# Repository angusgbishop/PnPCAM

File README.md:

# PnPCAM
 
PnPCAM is an [Open Hardware](https://www.oshwa.org/definition/) project dedicated to bringing high-quality machine vision to the various open source pick-and-place projects.

This project is very much **in development**, clone at your own risk!

The current versions of the board are based off the OnSemi AR0144 image sensor, as it is avaliable through mainline distributers at a reasonable cost for low quantities. 

* Up-to 1200x800 pixel resolution at 30fps (Currently limited by USB Bridge Chip)
* Global shutter
* Standard Webcam USB out
* <s>Onboard LED with exposure-triggered flash</s> (Requirement Dropped)
* LED Expansion Header for third-party use of the flash signal.
* Triggered shutter mode.
* Onboard lens distortion correction.

# Interested?
[View the Wiki here](https://github.com/angusgbishop/PnPCAM/wiki)

Find me on the [OpenPnP Discord](https://discord.gg/EmsrFVx)

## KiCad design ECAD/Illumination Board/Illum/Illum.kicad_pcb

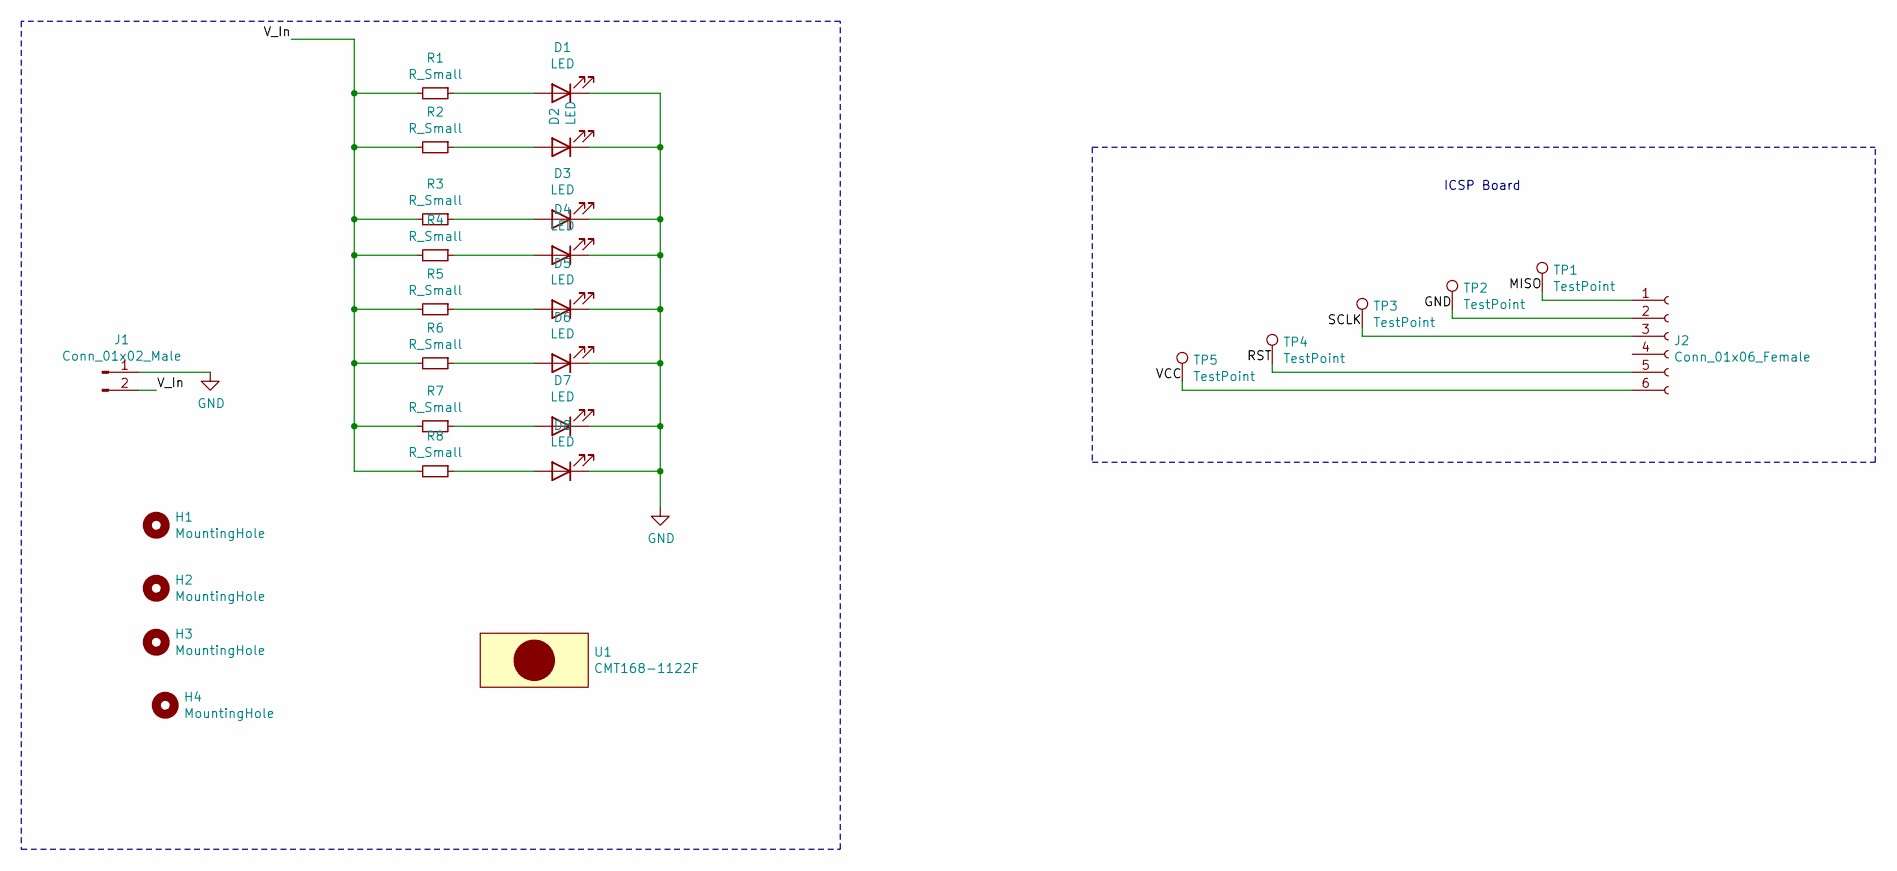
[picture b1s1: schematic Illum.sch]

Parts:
D1, D2, D3, D4, D5, D6, D7, D8: LED; LED_0805_2012Metric
H1, H2, H3, H4: MountingHole; MountingHole_2.2mm_M2_Pad_Via
J1: Conn_01x02_Male; PinHeader_1x02_P1.27mm_Vertical
J2: Conn_01x06_Female; PinHeader_2x03_P2.54mm_Vertical
R1, R2, R3, R4, R5, R6, R7, R8: R_Small; R_0402_1005Metric
TP1, TP2, TP3, TP4, TP5: TestPoint; PinHeader_1x01_P1.00mm_Vertical
U1: CMT168-1122F

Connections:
/MISO: J2.1, TP1.1
/RST: J2.5, TP4.1
/SCLK: J2.3, TP3.1
/VCC: J2.6, TP5.1
/V_In: J1.2, R1.2, R2.2, R3.2, R4.2, R5.2, R6.2, R7.2, R8.2
GND: D1.1 (K), D2.1 (K), D3.1 (K), D4.1 (K), D5.1 (K), D6.1 (K), D7.1 (K), D8.1 (K), J1.1, J2.2, TP2.1
unnamed: D1.2 (A), R1.1
unnamed: D2.2 (A), R2.1
unnamed: D3.2 (A), R3.1
unnamed: D4.2 (A), R4.1
unnamed: D5.2 (A), R5.1
unnamed: D6.2 (A), R6.1
unnamed: D7.2 (A), R7.1
unnamed: D8.2 (A), R8.1

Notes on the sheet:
ICSP Board

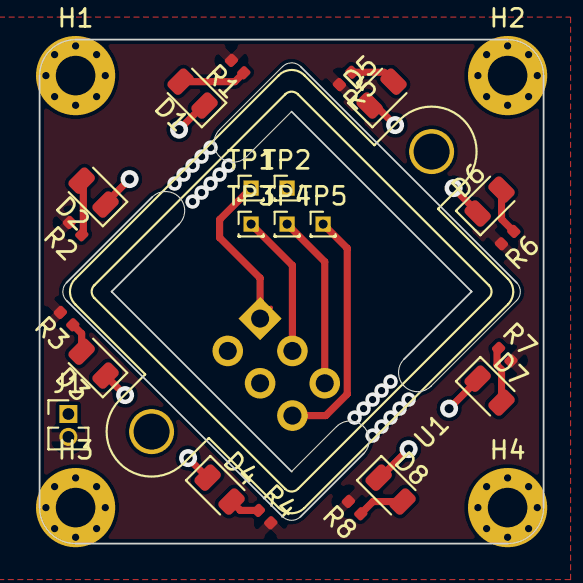
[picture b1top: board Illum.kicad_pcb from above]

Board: 2 copper layers, 28.0 x 28.0 mm, 28 parts (1 on the bottom side), 14 nets.

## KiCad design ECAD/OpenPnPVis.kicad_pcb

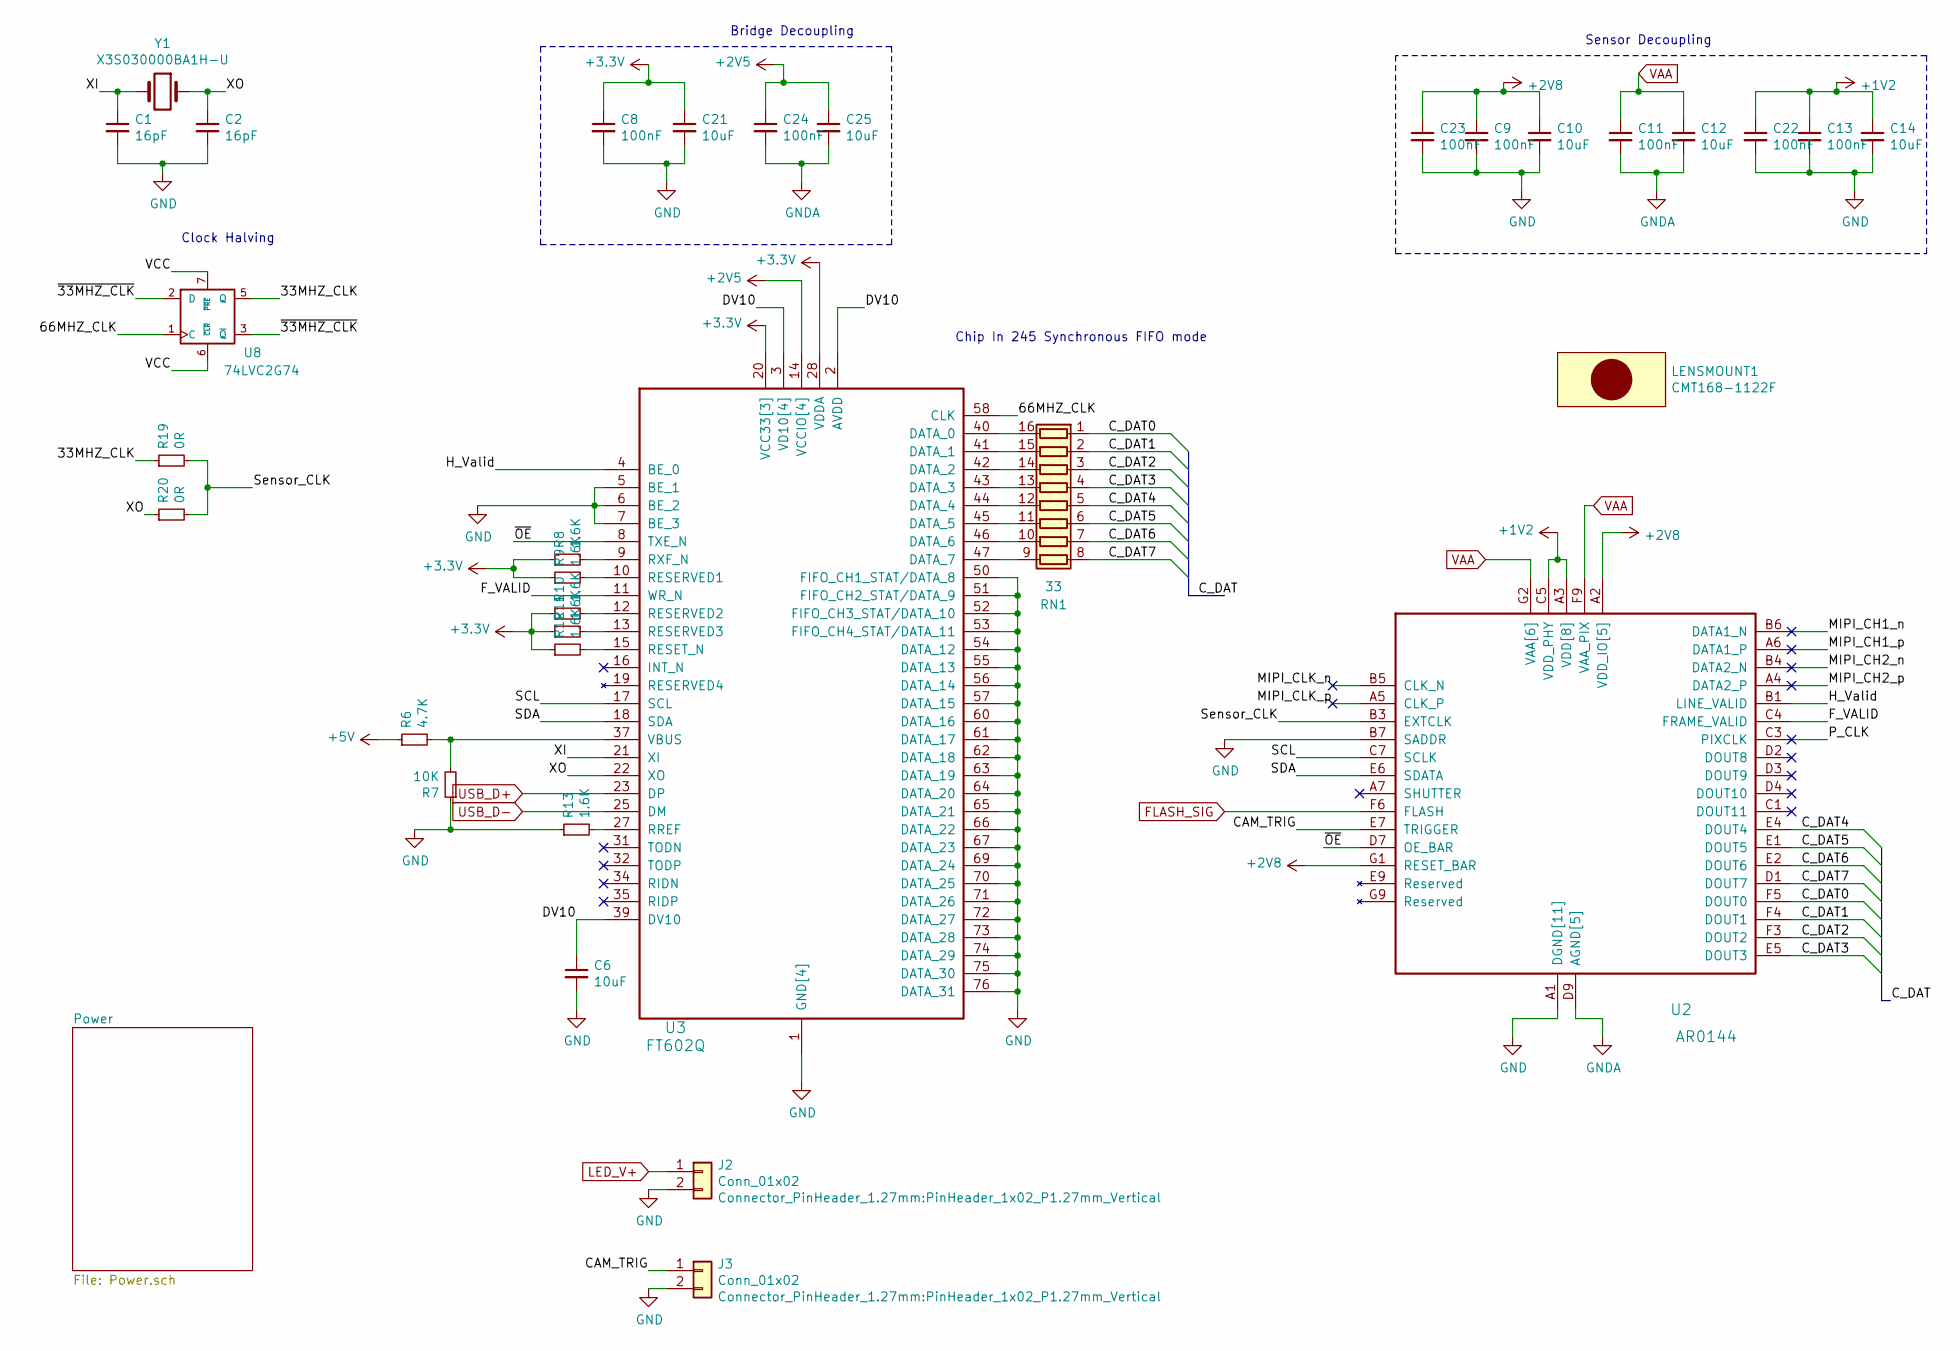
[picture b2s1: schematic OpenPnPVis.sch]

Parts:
C1, C2: 16pF; C_0402_1005Metric; MPN CC0402JRNPO9BN160
C6, C10, C12, C14, C21, C25: 10uF; C_0805_2012Metric_Pad1.15x1.40mm_HandSolder; MPN CL21A106KOQNNNE
C8, C9, C11, C13, C22, C23, C24: 100nF; C_0402_1005Metric; MPN CC0402KRX7R7BB104
J2, J3: Conn_01x02; PinHeader_1x02_P1.27mm_Vertical
LENSMOUNT1: CMT168-1122F; MPN N/A
R6: 4.7K; R_0402_1005Metric; MPN RC0402FR-074K7L
R7: 10K; R_0402_1005Metric; MPN RC0402JR-0710KL
R8, R9, R10, R11, R12, R13: 1.6K; R_0402_1005Metric; MPN RC0402FR-071K5L
R19, R20: 0R; R_0402_1005Metric; MPN RC0402FR-070RL
RN1: 33; R_Array_Convex_8x0602; MPN EXB2HV330JV
U2: ﻿AR0144; BGA-72_9x8_5.565x5.545mm; MPN AR0144
U3: FT602Q; QFN-76-1EP_9x9mm_P0.4mm_EP3.8x3.8mm; MPN FT602Q-B-T
U8: 74LVC2G74; VSSOP-8_2.4x2.1mm_P0.5mm; MPN 74LVC2G74
Y1: X3S030000BA1H-U; Crystal_SMD_3225-4Pin_3.2x2.5mm; MPN X3S030000BA1H-U

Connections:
+1V2: C13.1, C14.1, C22.1, U2.A3 (VDD[8]), U2.B2 (VDD[8]), U2.C5 (VDD_PHY), U2.C6 (VDD[8]), U2.D8 (VDD[8]), U2.F2 (VDD[8]), U2.G4 (VDD[8]), U2.G5 (VDD[8]), U2.G6 (VDD[8]); also elsewhere on the board
+2V8: C9.1, C10.1, C23.1, U2.A2 (VDD_IO[5]), U2.B8 (VDD_IO[5]), U2.C2 (VDD_IO[5]), U2.C8 (VDD_IO[5]), U2.E3 (VDD_IO[5]), U2.G1 (RESET_BAR), U8.6 (~CLR), U8.7 (~PRE), U8.8 (VCC); also elsewhere on the board
+3V3: C8.1, C21.1, R8.1, R9.1, R10.1, R11.1, R12.1, U3.20 (VCC33[3]), U3.24 (VCC33[3]), U3.28 (VDDA), U3.38 (VCC33[3]); also elsewhere on the board
+5V: R6.1; also elsewhere on the board
/33MHZ_CLK: R19.1, U8.5 (Q)
/66MHZ_CLK: U3.58 (CLK), U8.1 (C)
/CAM_TRIG: J3.1, U2.E7 (TRIGGER)
/C_DAT0: RN1.1 (R1.1), U2.F5 (DOUT0)
/C_DAT1: RN1.2 (R2.1), U2.F4 (DOUT1)
/C_DAT2: RN1.3 (R3.1), U2.F3 (DOUT2)
/C_DAT3: RN1.4 (R4.1), U2.E5 (DOUT3)
/C_DAT4: RN1.5 (R5.1), U2.E4 (DOUT4)
/C_DAT5: RN1.6 (R6.1), U2.E1 (DOUT5)
/C_DAT6: RN1.7 (R7.1), U2.E2 (DOUT6)
/C_DAT7: RN1.8 (R8.1), U2.D1 (DOUT7)
/DV10: C6.1, U3.2 (AVDD), U3.3 (VD10[4]), U3.30 (VD10[4]), U3.33 (VD10[4]), U3.39 (DV10), U3.48 (VD10[4])
/F_VALID: U2.C4 (FRAME_VALID), U3.11 (WR_N)
/H_Valid: U2.B1 (LINE_VALID), U3.4 (BE_0)
/MIPI_CH1_n: U2.B6 (DATA1_N)
/MIPI_CH1_p: U2.A6 (DATA1_P)
/MIPI_CH2_n: U2.B4 (DATA2_N)
/MIPI_CH2_p: U2.A4 (DATA2_P)
/MIPI_CLK_n: U2.B5 (CLK_N)
/MIPI_CLK_p: U2.A5 (CLK_P)
/P_CLK: U2.C3 (PIXCLK)
/SCL: U2.C7 (SCLK), U3.17 (SCL)
/SDA: U2.E6 (SDATA), U3.18 (SDA)
/Sensor_CLK: R19.2, R20.2, U2.B3 (EXTCLK)
/XI: C1.1, U3.21 (XI), Y1.2
/XO: C2.1, R20.1, U3.22 (XO), Y1.1
/~33MHZ_CLK: U8.2 (D), U8.3 (~Q)
/~OE: U2.D7 (OE_BAR), U3.8 (TXE_N)
FLASH_SIG: U2.F6 (FLASH); also elsewhere on the board
GND: C1.2, C2.2, C6.2, C8.2, C9.2, C10.2, C11.2, C12.2, C13.2, C14.2, C21.2, C22.2, C23.2, C24.2, C25.2, J2.2, J3.2, R7.1, R13.1, U2.A1 (DGND[11]), U2.A8 (DGND[11]), U2.B7 (SADDR), U2.D5 (DGND[11]), U2.D6 (DGND[11]), U2.D9 (AGND[5]), U2.E8 (DGND[11]), U2.F1 (DGND[11]), U2.F7 (DGND[11]), U2.F8 (DGND[11]), U2.G3 (AGND[5]), U2.G7 (AGND[5]), U2.H3 (AGND[5]), U2.H4 (DGND[11]), U2.H5 (DGND[11]), U2.H6 (DGND[11]), U2.H7 (AGND[5]), U3.1 (GND[4]), U3.5 (BE_1), U3.6 (BE_2), U3.7 (BE_3), U3.26 (GND[4]), U3.29 (GND[4]), U3.36 (GND[4]), U3.50 (FIFO_CH1_STAT/DATA_8), U3.51 (FIFO_CH2_STAT/DATA_9), U3.52 (FIFO_CH3_STAT/DATA_10), U3.53 (FIFO_CH4_STAT/DATA_11), U3.54 (DATA_12), U3.55 (DATA_13), U3.56 (DATA_14), U3.57 (DATA_15), U3.60 (DATA_16), U3.61 (DATA_17), U3.62 (DATA_18), U3.63 (DATA_19), U3.64 (DATA_20), U3.65 (DATA_21), U3.66 (DATA_22), U3.67 (DATA_23), U3.69 (DATA_24), U3.70 (DATA_25), U3.71 (DATA_26), U3.72 (DATA_27), U3.73 (DATA_28), U3.74 (DATA_29), U3.75 (DATA_30), U3.76 (DATA_31), U3.77 (GND[4]), U8.4 (GND); also elsewhere on the board
LED_V+: J2.1; also elsewhere on the board
unnamed: R6.2, R7.2, U3.37 (VBUS)
unnamed: R8.2, U3.9 (RXF_N)
unnamed: R9.2, U3.10 (RESERVED1)
unnamed: R10.2, U3.12 (RESERVED2)
unnamed: R11.2, U3.13 (RESERVED3)
unnamed: R12.2, U3.15 (RESET_N)
unnamed: R13.2, U3.27 (RREF)
unnamed: RN1.9 (R8.2), U3.47 (DATA_7)
unnamed: RN1.10 (R7.2), U3.46 (DATA_6)
unnamed: RN1.11 (R6.2), U3.45 (DATA_5)
unnamed: RN1.12 (R5.2), U3.44 (DATA_4)
unnamed: RN1.13 (R4.2), U3.43 (DATA_3)
unnamed: RN1.14 (R3.2), U3.42 (DATA_2)
unnamed: RN1.15 (R2.2), U3.41 (DATA_1)
unnamed: RN1.16 (R1.2), U3.40 (DATA_0)
USB_D+: U3.23 (DP); also elsewhere on the board
USB_D-: U3.25 (DM); also elsewhere on the board
VAA: C11.1, C12.1, C24.1, C25.1, U2.F9 (VAA_PIX), U2.G2 (VAA[6]), U2.G8 (VAA[6]), U2.H1 (VAA[6]), U2.H2 (VAA[6]), U2.H8 (VAA[6]), U2.H9 (VAA[6]), U3.14 (VCCIO[4]), U3.49 (VCCIO[4]), U3.59 (VCCIO[4]), U3.68 (VCCIO[4]); also elsewhere on the board

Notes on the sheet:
Sensor Decoupling
Clock Halving
Chip In 245 Synchronous FIFO mode
Bridge Decoupling

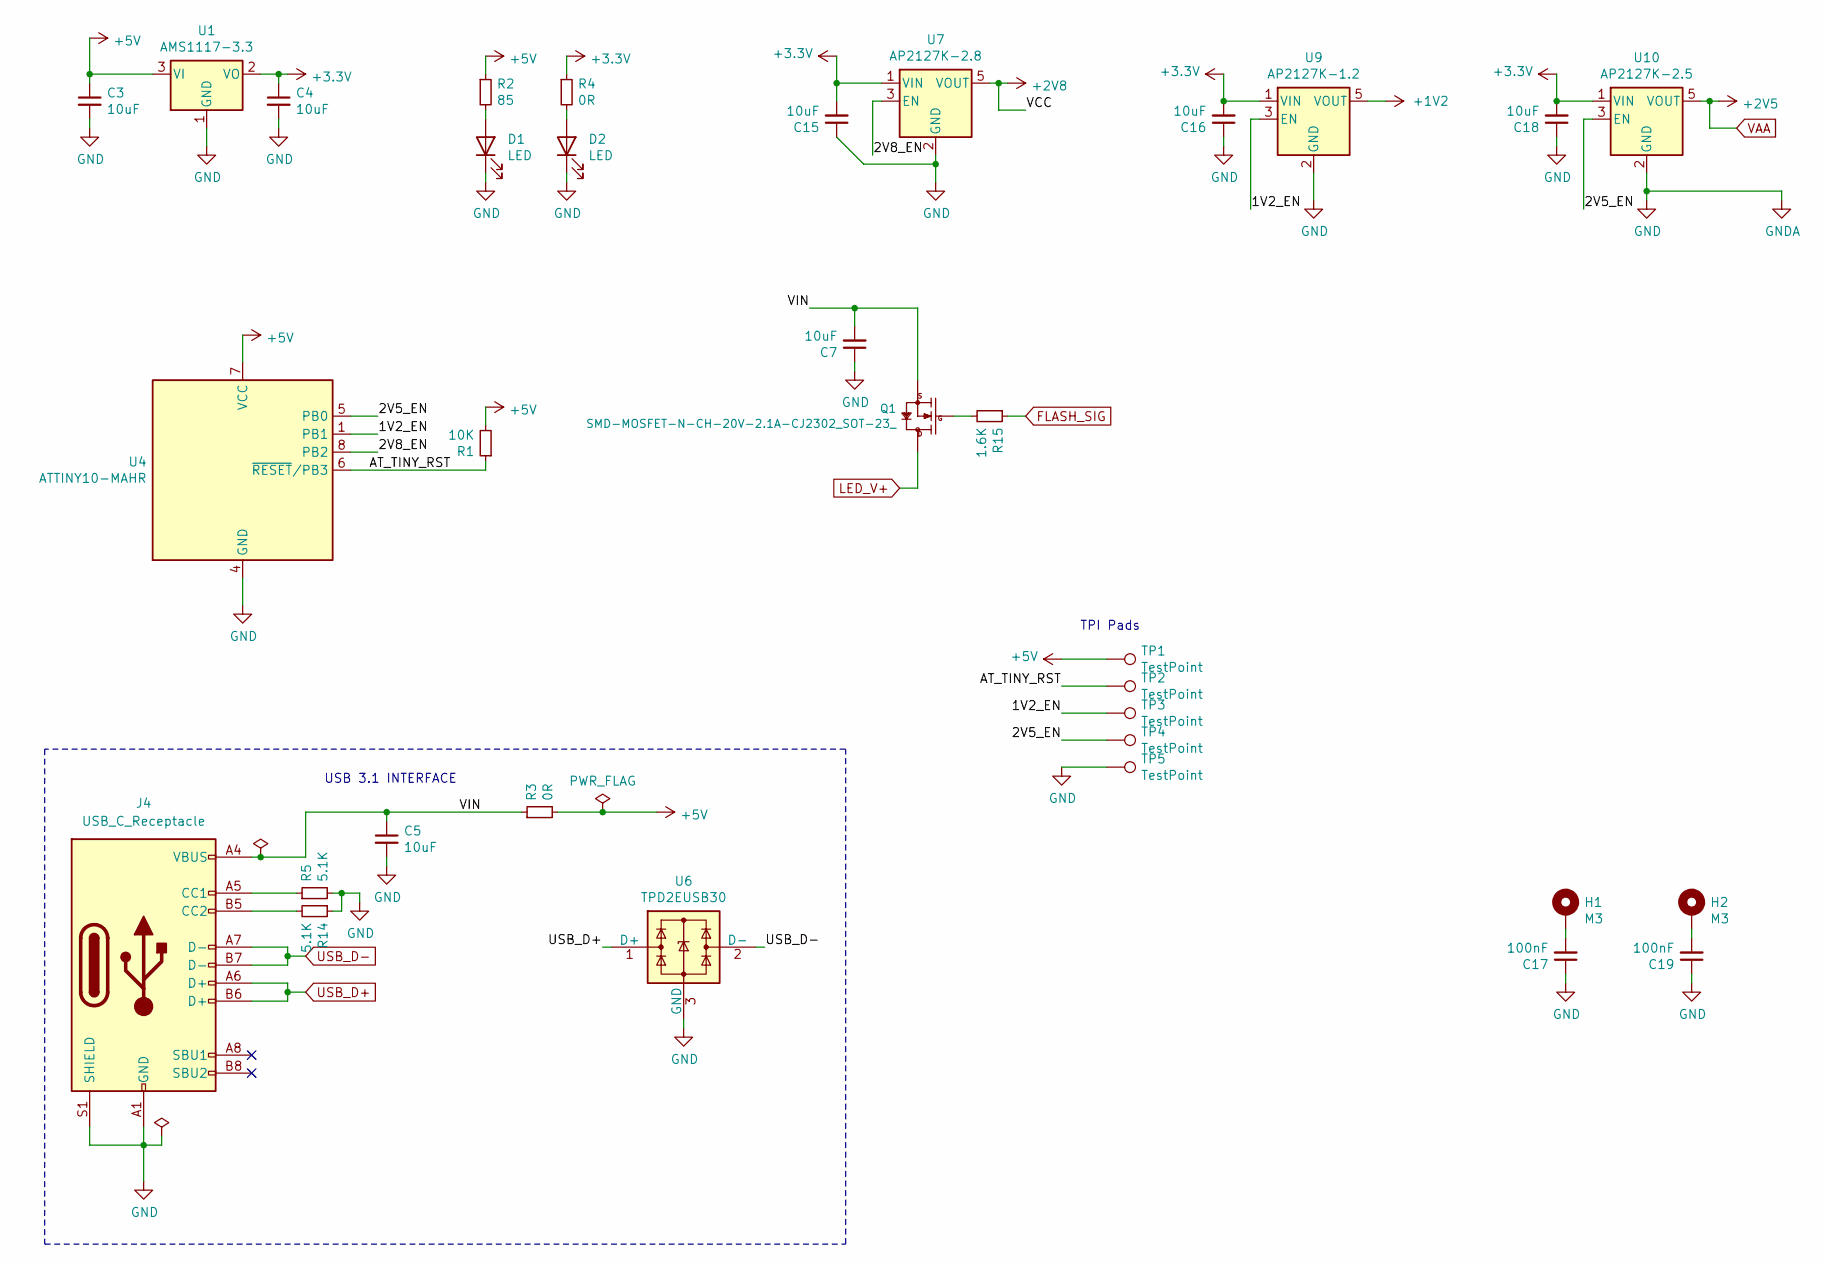
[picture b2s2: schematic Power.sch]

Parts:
C3, C4, C5, C7, C15, C16, C18: 10uF; C_0805_2012Metric_Pad1.15x1.40mm_HandSolder; MPN CL21A106KOQNNNE
C17, C19: 100nF; C_0402_1005Metric; MPN CC0402KRX7R7BB104
D1, D2: LED; LED_0805_2012Metric; MPN ORH-B35A
H1, H2: M3; MountingHole_2.2mm_M2_Pad_Via; MPN N/A
J4: USB_C_Receptacle; HRO-TYPE-C-31-M-12-Assembly; MPN TYPE-C-31-M-12
Q1: SMD-MOSFET-N-CH-20V-2.1A-CJ2302_SOT-23_; SOT-23; MPN CJ2302
R1: 10K; R_0402_1005Metric; MPN RC0402JR-0710KL
R2: 85; R_0402_1005Metric; MPN RC0402FR-0785RL
R3, R4: 0R; R_0402_1005Metric; MPN RC0402FR-070RL
R5, R14: 5.1K; R_0402_1005Metric; MPN RC0402FR-075K1L
R15: 1.6K; R_0402_1005Metric; MPN RC0402FR-070RL
TP1, TP2, TP3, TP4, TP5: TestPoint; TestPoint_Pad_1.0x1.0mm
U1: AMS1117-3.3; SOT-223-3_TabPin2; MPN AMS1117-3.3
U4: ATTINY10-MAHR; DFN-8-1EP_2x2mm_P0.5mm_EP0.9x1.5mm; MPN ATTINY10-MAHR
U6: TPD2EUSB30; Texas_DRT-3; MPN TPD2EUSB30
U7: AP2127K-2.8; SOT-23-5; MPN AP2127K-2.8
U9: AP2127K-1.2; SOT-23-5; MPN AP2127K-1.2
U10: AP2127K-2.5; SOT-23-5; MPN AP2127K-2.5

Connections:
+1V2: U9.5 (VOUT); also elsewhere on the board
+2V8: U7.5 (VOUT); also elsewhere on the board
+3V3: C4.1, C15.2, C16.2, C18.2, R4.1, U1.2 (VO), U7.1 (VIN), U9.1 (VIN), U10.1 (VIN); also elsewhere on the board
+5V: C3.1, R1.2, R2.1, R3.2, TP1.1, U1.3 (VI), U4.7 (VCC); also elsewhere on the board
/Power/1V2_EN: TP3.1, U4.1 (PB1), U9.3 (EN)
/Power/2V5_EN: TP4.1, U4.5 (PB0), U10.3 (EN)
/Power/2V8_EN: U4.8 (PB2), U7.3 (EN)
/Power/AT_TINY_RST: R1.1, TP2.1, U4.6 (~RESET~/PB3)
/Power/VIN: C5.1, C7.2, J4.A4 (VBUS), J4.A9 (VBUS), J4.B4 (VBUS), J4.B9 (VBUS), Q1.2 (S), R3.1
FLASH_SIG: R15.1; also elsewhere on the board
GND: C3.2, C4.2, C5.2, C7.1, C15.1, C16.1, C17.1, C18.1, C19.1, D1.1 (K), D2.1 (K), J4.A1 (GND), J4.A12 (GND), J4.B1 (GND), J4.B12 (GND), J4.S1 (SHIELD), R5.2, R14.1, TP5.1, U1.1 (GND), U4.4 (GND), U6.3 (GND), U7.2 (GND), U9.2 (GND), U10.2 (GND); also elsewhere on the board
LED_V+: Q1.3 (D); also elsewhere on the board
unnamed: C17.2, H1.1
unnamed: C19.2, H2.1
unnamed: D1.2 (A), R2.2
unnamed: D2.2 (A), R4.2
unnamed: J4.A5 (CC1), R5.1
unnamed: J4.B5 (CC2), R14.2
unnamed: Q1.1 (G), R15.2
USB_D+: J4.A6 (D+), J4.B6 (D+), U6.1 (D+); also elsewhere on the board
USB_D-: J4.A7 (D-), J4.B7 (D-), U6.2 (D-); also elsewhere on the board
VAA: U10.5 (VOUT); also elsewhere on the board

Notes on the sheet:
USB 3.1 INTERFACE
TPI Pads

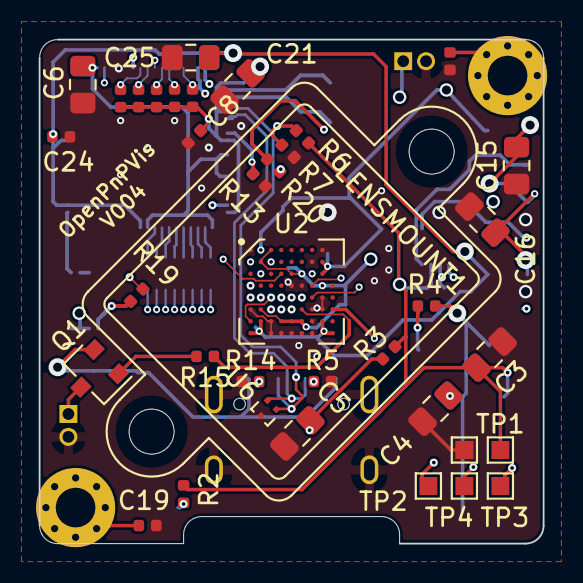
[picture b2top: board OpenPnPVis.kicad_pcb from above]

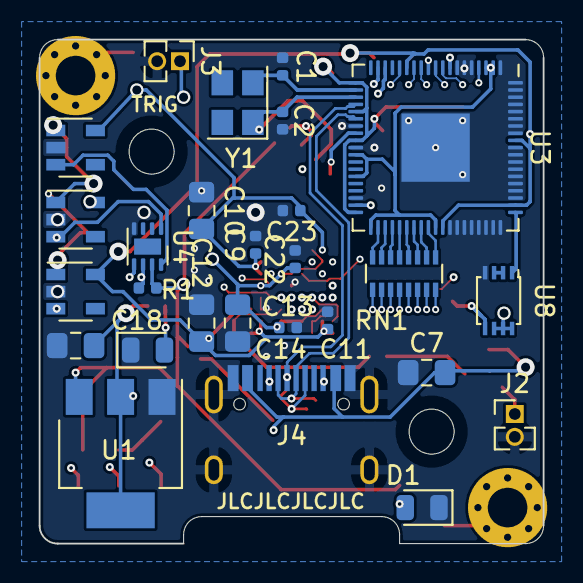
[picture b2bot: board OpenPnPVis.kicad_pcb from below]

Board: 4 copper layers, 28.0 x 28.0 mm, 66 parts (27 on the bottom side), 58 nets.

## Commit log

2020-12-06 First Commit
    Commit of V002
2020-12-13 Changed FT602Q and AR0144 Libraries to Common project library.
2020-12-13 Added Courtyard to Lens mount
2020-12-14 Tidied Schematic and added more to readme
2020-12-14 Updated Crystal and LED Resistors
    Updated Crystal Capacitors to 16pF and 5V series resistors for LED's to 85Ohm.
2020-12-17 Library Updates
    Added stp files for the lens mount, mounting screws, and image sensor.
2020-12-17 Creation of Rev003
    Creation of Rev003. This is a mini-sized board for easier fitment into tight spaces. The USB connector has changed to a USB Type-C. Some components have changed footprint to 0402.
2020-12-17 Remove backup files
2021-01-28 V004 Update
    Added ICSP pads
    Updated 74LVC2G74 footprint
2021-01-28 V001 Illumination Board
    Creation of Illumination board and Programming board for Camera.
2021-02-12 Library Tweaks
    Twaks to libraries
    Illumination board updates
2021-02-15 V005 Release
    V0005 Replaces the ATTINY10 with an ATTINY1606, It also adds a breakaway expansion I/O and programming header.
    The ATTINY is now on the I2C bus, and the flip/flop reset is now tied to the ATTINY GPIO.
